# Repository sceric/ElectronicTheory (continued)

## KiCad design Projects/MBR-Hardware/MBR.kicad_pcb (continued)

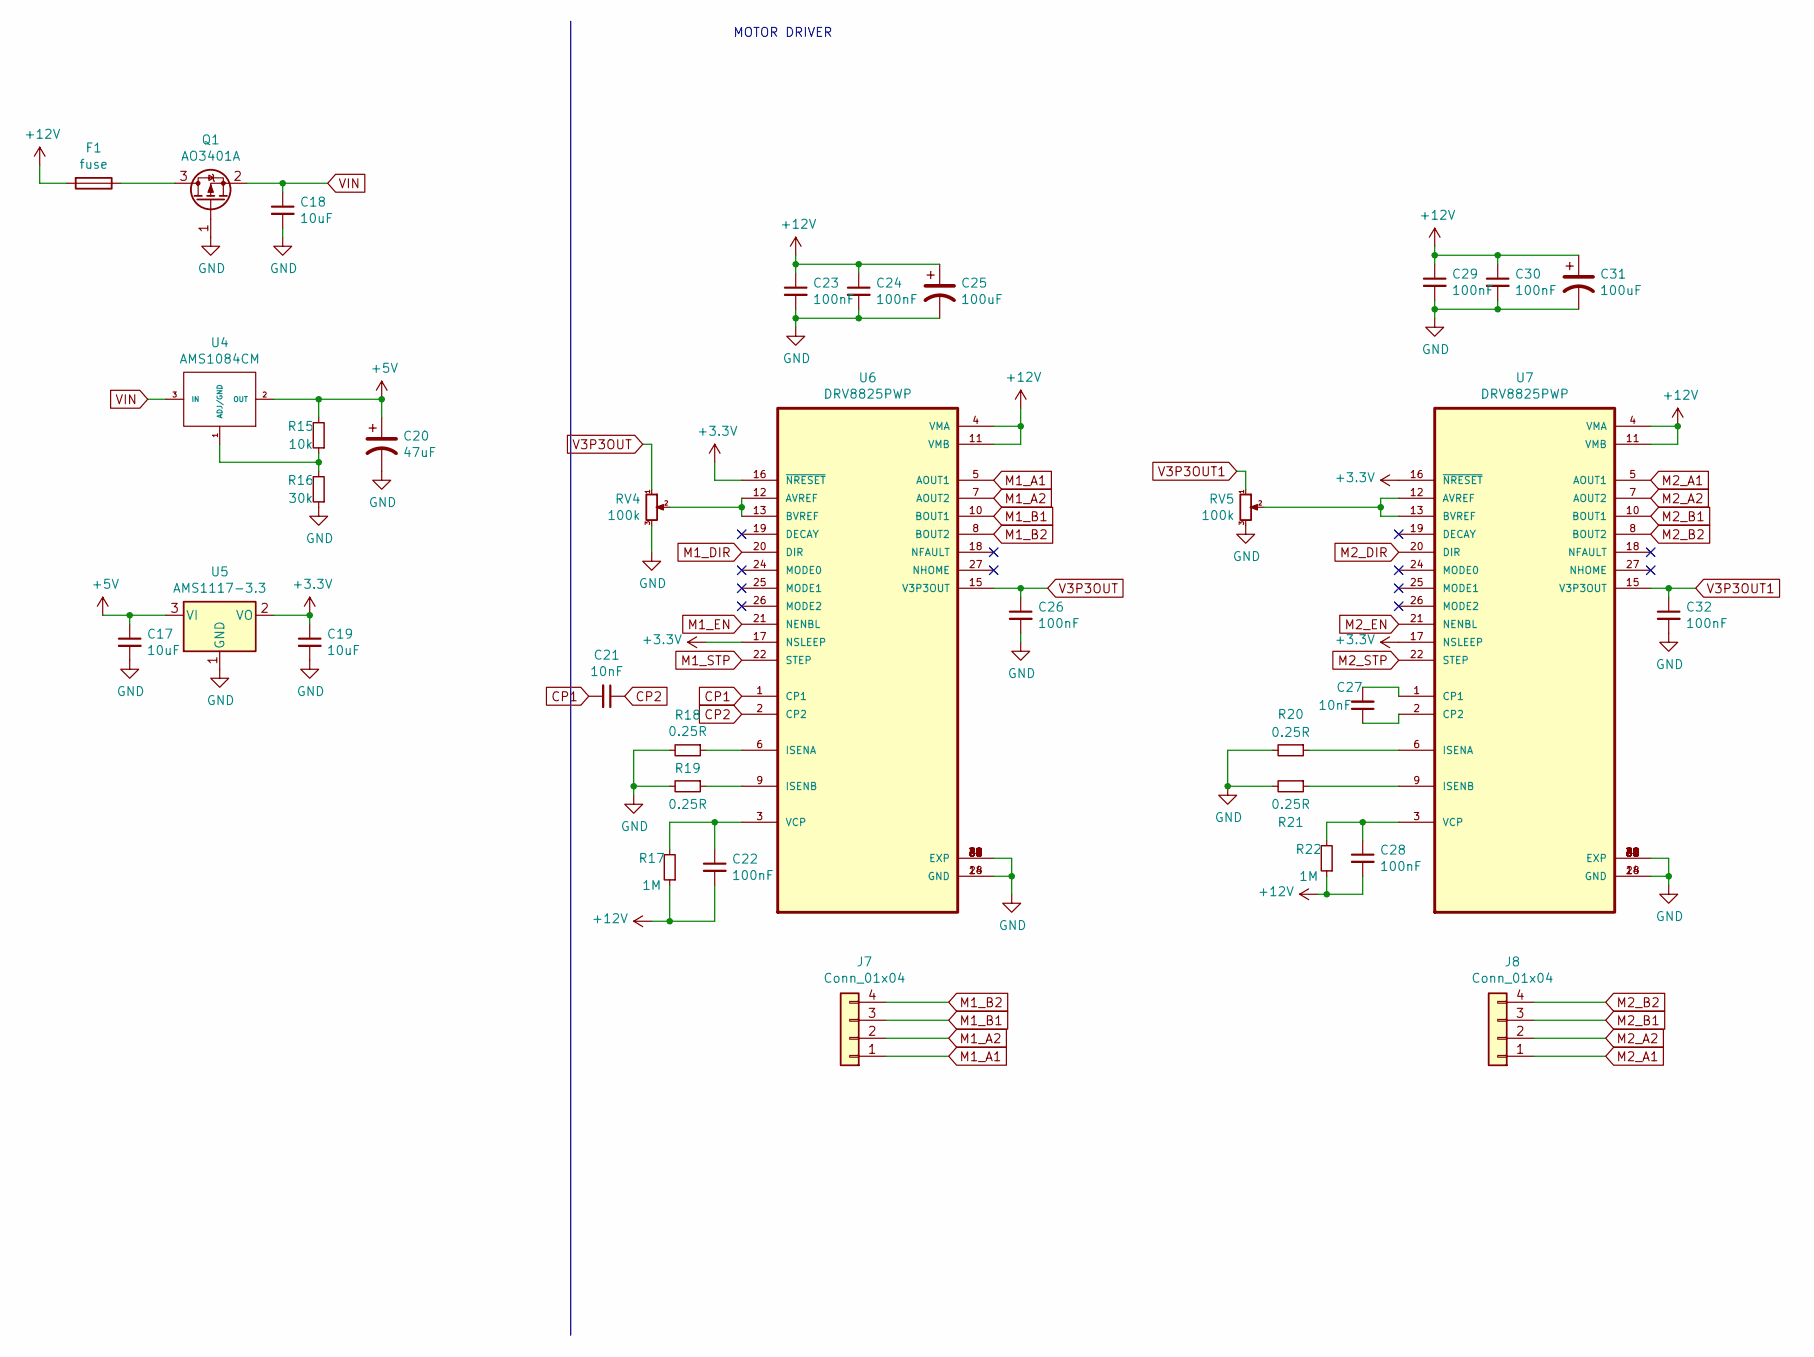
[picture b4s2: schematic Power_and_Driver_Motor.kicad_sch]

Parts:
C17, C18, C19: 10uF; C_0805_2012Metric
C20: 47uF; CP_Elec_6.3x5.4
C21, C27: 10nF; C_0603_1608Metric
C22, C23, C24, C26, C28, C29, C30, C32: 100nF; C_0603_1608Metric
C25, C31: 100uF; CP_Elec_8x10
F1: fuse; Fuse_1812_4532Metric
J7, J8: Conn_01x04; PinHeader_1x04_P2.54mm_Vertical
Q1: AO3401A; SOT-23
R15: 10k; R_0603_1608Metric
R16: 30k; R_0603_1608Metric
R17, R22: 1M; R_0603_1608Metric
R18, R19, R20, R21: 0.25R; R_0805_2012Metric
RV4, RV5: 100k; Potentiometer_Bourns_TC33X_Vertical
U4: AMS1084CM; TO-263-3_TabPin4
U5: AMS1117-3.3; SOT-223-3_TabPin2
U6, U7: DRV8825PWP; IC_TPS61196PWPRQ1

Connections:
+3V3: C19.1, U5.2 (VO), U6.16 (~NRESET), U6.17 (NSLEEP), U7.16 (~NRESET), U7.17 (NSLEEP); also elsewhere on the board
+5V: C17.1, C20.1, R15.2, U4.2 (OUT), U5.3 (VI); also elsewhere on the board
+12V: C22.2, C23.1, C24.1, C25.1, C28.2, C29.1, C30.1, C31.1, F1.2, R17.1, R22.1, U6.4 (VMA), U6.11 (VMB), U7.4 (VMA), U7.11 (VMB); also elsewhere on the board
CP1: C21.2, U6.1 (CP1)
CP2: C21.1, U6.2 (CP2)
GND: C17.2, C18.2, C19.2, C20.2, C23.2, C24.2, C25.2, C26.2, C29.2, C30.2, C31.2, C32.2, Q1.1 (G), R16.1, R18.2, R19.2, R20.2, R21.2, RV4.3, RV5.3, U5.1 (GND), U6.14 (GND), U6.28 (GND), U6.29 (EXP), U6.30 (EXP), U6.31 (EXP), U6.32 (EXP), U6.33 (EXP), U6.34 (EXP), U6.35 (EXP), U6.36 (EXP), U6.37 (EXP), U6.38 (EXP), U6.39 (EXP), U6.40 (EXP), U6.41 (EXP), U6.42 (EXP), U6.43 (EXP), U6.44 (EXP), U6.45 (EXP), U6.46 (EXP), U6.47 (EXP), U6.48 (EXP), U6.49 (EXP), U6.50 (EXP), U7.14 (GND), U7.28 (GND), U7.29 (EXP), U7.30 (EXP), U7.31 (EXP), U7.32 (EXP), U7.33 (EXP), U7.34 (EXP), U7.35 (EXP), U7.36 (EXP), U7.37 (EXP), U7.38 (EXP), U7.39 (EXP), U7.40 (EXP), U7.41 (EXP), U7.42 (EXP), U7.43 (EXP), U7.44 (EXP), U7.45 (EXP), U7.46 (EXP), U7.47 (EXP), U7.48 (EXP), U7.49 (EXP), U7.50 (EXP); also elsewhere on the board
M1_A1: J7.1, U6.5 (AOUT1)
M1_A2: J7.2, U6.7 (AOUT2)
M1_B1: J7.3, U6.10 (BOUT1)
M1_B2: J7.4, U6.8 (BOUT2)
M1_DIR: U6.20 (DIR); also elsewhere on the board
M1_EN: U6.21 (NENBL); also elsewhere on the board
M1_STP: U6.22 (STEP); also elsewhere on the board
M2_A1: J8.1, U7.5 (AOUT1)
M2_A2: J8.2, U7.7 (AOUT2)
M2_B1: J8.3, U7.10 (BOUT1)
M2_B2: J8.4, U7.8 (BOUT2)
M2_DIR: U7.20 (DIR); also elsewhere on the board
M2_EN: U7.21 (NENBL); also elsewhere on the board
M2_STP: U7.22 (STEP); also elsewhere on the board
unnamed: C22.1, R17.2, U6.3 (VCP)
unnamed: C27.1, U7.2 (CP2)
unnamed: C27.2, U7.1 (CP1)
unnamed: C28.1, R22.2, U7.3 (VCP)
unnamed: F1.1, Q1.3 (D)
unnamed: R15.1, R16.2, U4.1 (ADJ/GND)
unnamed: R18.1, U6.6 (ISENA)
unnamed: R19.1, U6.9 (ISENB)
unnamed: R20.1, U7.6 (ISENA)
unnamed: R21.1, U7.9 (ISENB)
unnamed: RV4.2, U6.12 (AVREF), U6.13 (BVREF)
unnamed: RV5.2, U7.12 (AVREF), U7.13 (BVREF)
V3P3OUT: C26.1, RV4.1, U6.15 (V3P3OUT)
V3P3OUT1: C32.1, RV5.1, U7.15 (V3P3OUT)
VIN: C18.1, Q1.2 (S), U4.3 (IN)

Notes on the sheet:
MOTOR DRIVER

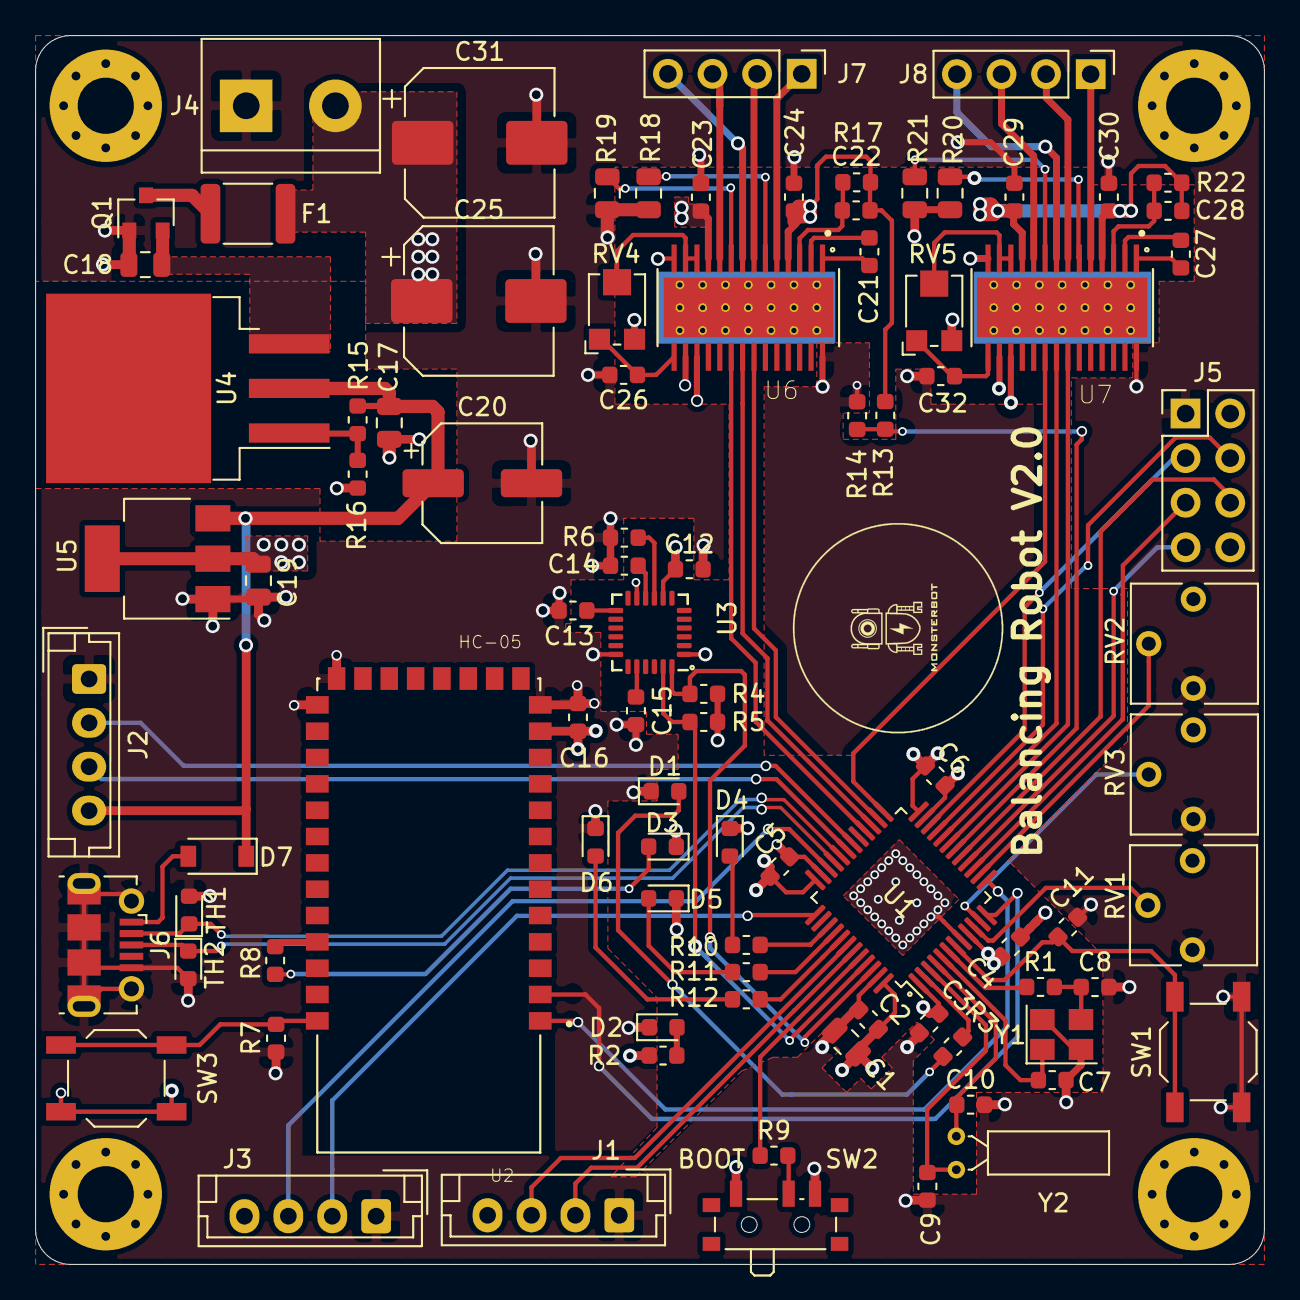
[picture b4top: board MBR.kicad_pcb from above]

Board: 4 copper layers, 70.0 x 70.0 mm, 94 parts (0 on the bottom side), 81 nets.

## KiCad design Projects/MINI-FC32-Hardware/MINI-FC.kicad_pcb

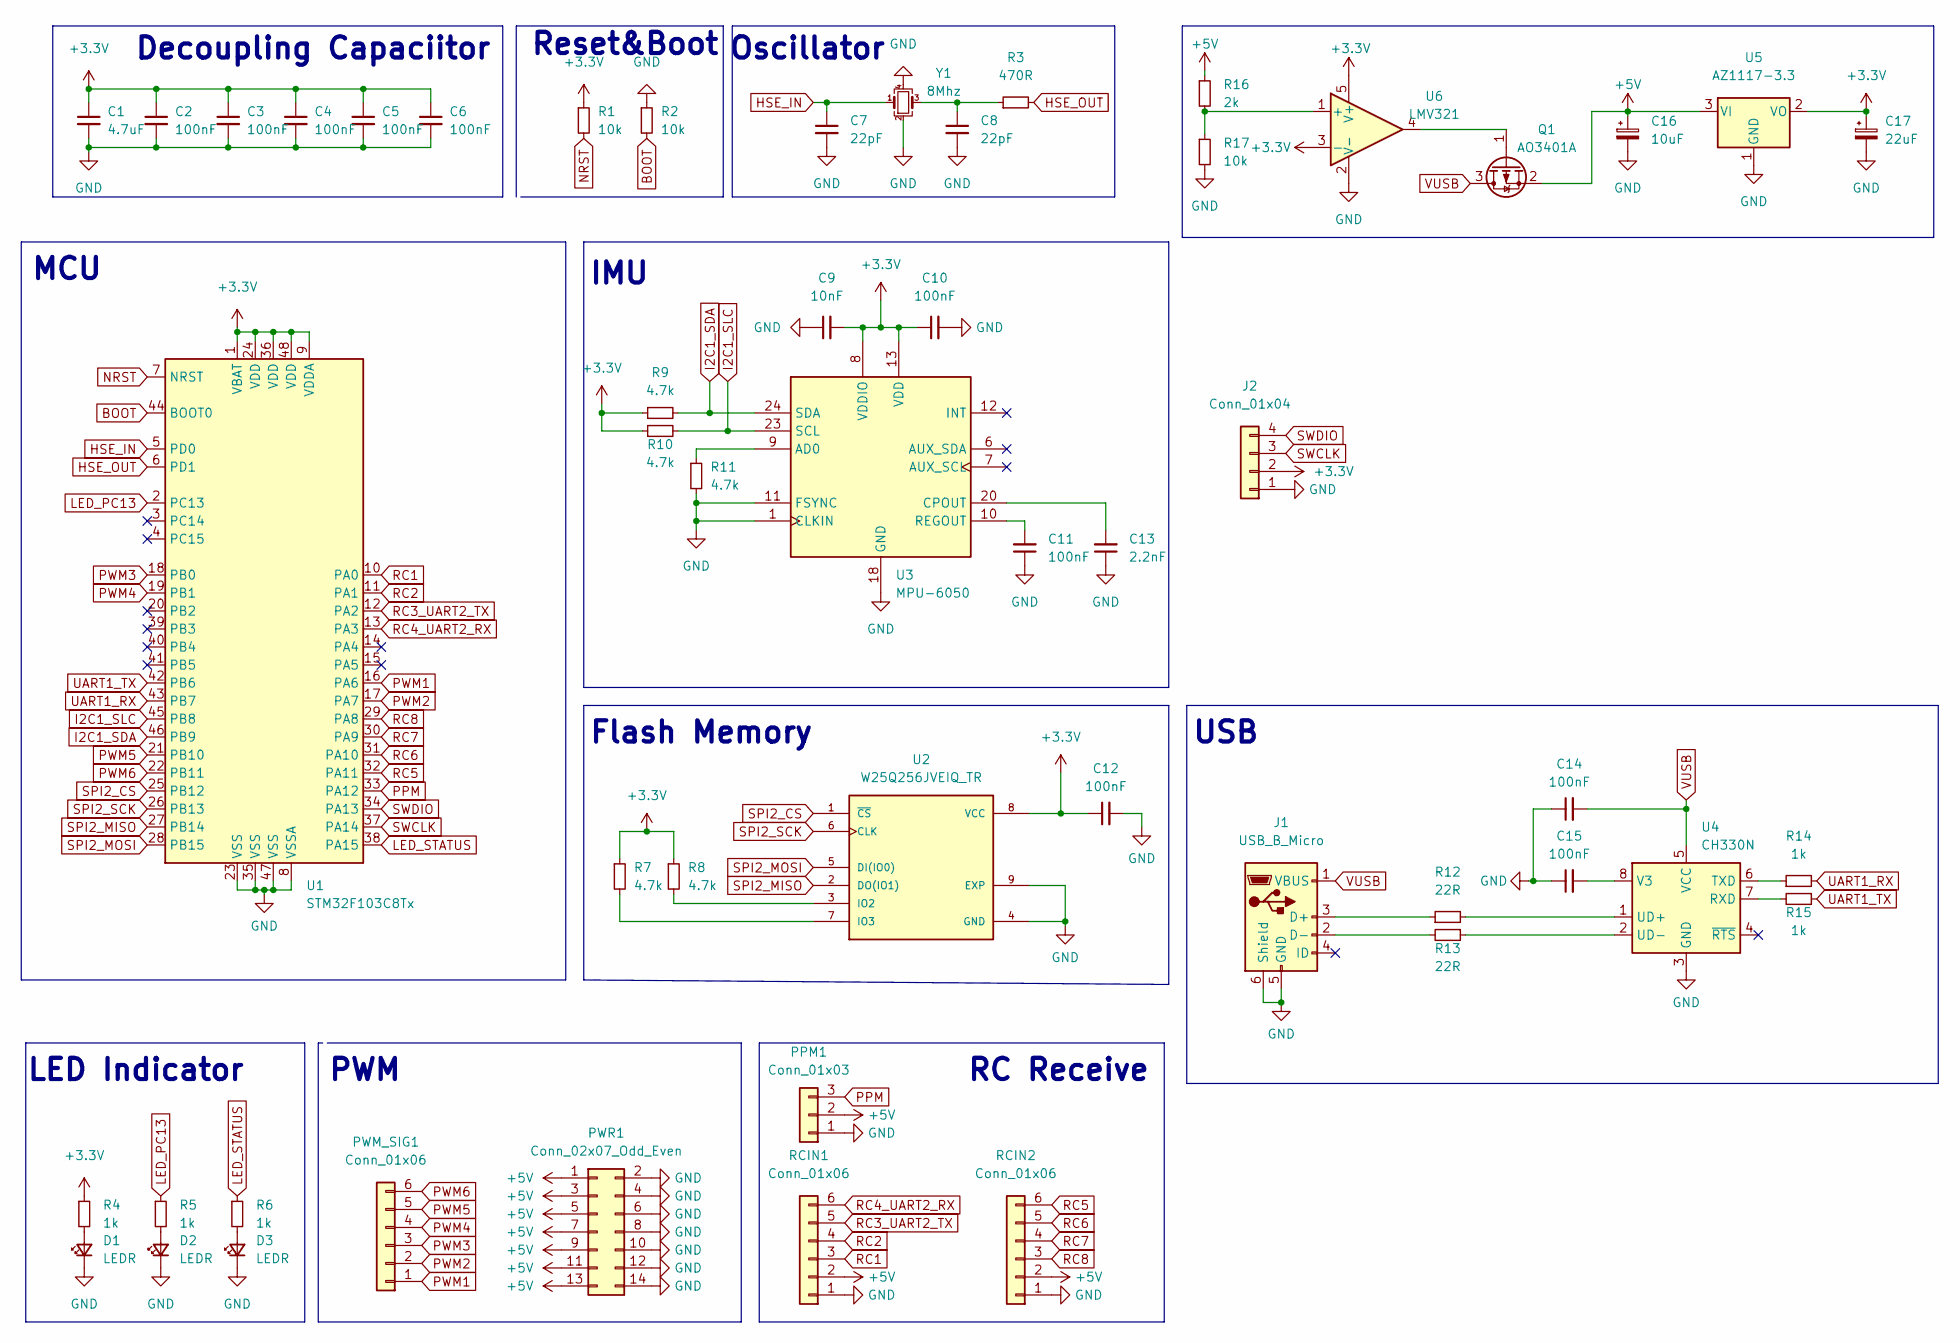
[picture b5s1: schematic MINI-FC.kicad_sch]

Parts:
C1: 4.7uF; C_0805_2012Metric
C2, C3, C4, C5, C6, C10, C11, C12, C14, C15: 100nF; C_0603_1608Metric
C7, C8: 22pF; C_0603_1608Metric
C9: 10nF; C_0603_1608Metric
C13: 2.2nF; C_0603_1608Metric
C16: 10uF; CP_EIA-3216-10_Kemet-I
C17: 22uF; CP_EIA-3216-10_Kemet-I
D1, D2, D3: LEDR; LED_0603_1608Metric
J1: USB_B_Micro; USB_Micro-B_Molex-105017-0001
J2: Conn_01x04; ConPadx04
PPM1: Conn_01x03; Molex_PicoBlade_53261-0371_1x03-1MP_P1.25mm_Horizontal
PWM_SIG1: Conn_01x06; PinHeader_1x06_P2.54mm_Vertical
PWR1: Conn_02x07_Odd_Even; PinHeader_2x07_P2.54mm_Vertical
Q1: AO3401A; SOT-23
R1, R2, R17: 10k; R_0603_1608Metric
R3: 470R; R_0603_1608Metric
R4, R5, R6, R14, R15: 1k; R_0603_1608Metric
R7, R8, R9, R10, R11: 4.7k; R_0603_1608Metric
R12, R13: 22R; R_0603_1608Metric
R16: 2k; R_0603_1608Metric
RCIN1, RCIN2: Conn_01x06; Molex_PicoBlade_53261-0671_1x06-1MP_P1.25mm_Horizontal
U1: STM32F103C8Tx; LQFP-48_7x7mm_P0.5mm
U2: W25Q256JVEIQ_TR; SON127P800X600X80-9N
U3: MPU-6050; InvenSense_QFN-24_4x4mm_P0.5mm
U4: CH330N; SOIC-8_3.9x4.9mm_P1.27mm
U5: AZ1117-3.3; SOT-89-3
U6: LMV321; SOT-23-5
Y1: 8Mhz; Crystal_SMD_3225-4Pin_3.2x2.5mm

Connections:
+3V3: C1.1, C2.1, C3.1, C4.1, C5.1, C6.1, C9.2, C10.1, C12.1, C17.1, J2.2, R1.1, R4.1, R7.1, R8.1, R9.1, R10.1, U1.1 (VBAT), U1.9 (VDDA), U1.24 (VDD), U1.36 (VDD), U1.48 (VDD), U2.8 (VCC), U3.8 (VDDIO), U3.13 (VDD), U5.2 (VO), U6.3 (-), U6.5 (V+)
+5V: C16.1, PPM1.2, PWR1.1, PWR1.3, PWR1.5, PWR1.7, PWR1.9, PWR1.11, PWR1.13, Q1.2 (S), R16.1, RCIN1.2, RCIN2.2, U5.3 (VI)
BOOT: R2.2, U1.44 (BOOT0)
GND: C1.2, C2.2, C3.2, C4.2, C5.2, C6.2, C7.2, C8.2, C9.1, C10.2, C11.1, C12.2, C13.1, C14.1, C15.1, C16.2, C17.2, D1.1 (K), D2.1 (K), D3.1 (K), J1.5 (GND), J1.6 (Shield), J2.1, PPM1.1, PWR1.2, PWR1.4, PWR1.6, PWR1.8, PWR1.10, PWR1.12, PWR1.14, R2.1, R11.2, R17.2, RCIN1.1, RCIN2.1, U1.8 (VSSA), U1.23 (VSS), U1.35 (VSS), U1.47 (VSS), U2.4 (GND), U2.9 (EXP), U3.1 (CLKIN), U3.11 (FSYNC), U3.18 (GND), U4.3 (GND), U5.1 (GND), U6.2 (V-), Y1.2, Y1.4
HSE_IN: C7.1, U1.5 (PD0), Y1.1
HSE_OUT: R3.2, U1.6 (PD1)
I2C1_SDA: R9.2, U1.46 (PB9), U3.24 (SDA)
I2C1_SLC: R10.2, U1.45 (PB8), U3.23 (SCL)
LED_PC13: R5.1, U1.2 (PC13)
LED_STATUS: R6.1, U1.38 (PA15)
NRST: R1.2, U1.7 (NRST)
unnamed: C8.1, R3.1, Y1.3
unnamed: C11.2, U3.10 (REGOUT)
unnamed: C13.2, U3.20 (CPOUT)
unnamed: C15.2, U4.8 (V3)
unnamed: D1.2 (A), R4.2
unnamed: D2.2 (A), R5.2
unnamed: D3.2 (A), R6.2
unnamed: J1.2 (D-), R13.2
unnamed: J1.3 (D+), R12.1
unnamed: Q1.1 (G), U6.4
unnamed: R7.2, U2.7 (IO3)
unnamed: R8.2, U2.3 (IO2)
unnamed: R11.1, U3.9 (AD0)
unnamed: R12.2, U4.1 (UD+)
unnamed: R13.1, U4.2 (UD-)
unnamed: R14.1, U4.6 (TXD)
unnamed: R15.2, U4.7 (RXD)
unnamed: R16.2, R17.1, U6.1 (+)
PPM: PPM1.3, U1.33 (PA12)
PWM1: PWM_SIG1.1, U1.16 (PA6)
PWM2: PWM_SIG1.2, U1.17 (PA7)
PWM3: PWM_SIG1.3, U1.18 (PB0)
PWM4: PWM_SIG1.4, U1.19 (PB1)
PWM5: PWM_SIG1.5, U1.21 (PB10)
PWM6: PWM_SIG1.6, U1.22 (PB11)
RC1: RCIN1.3, U1.10 (PA0)
RC2: RCIN1.4, U1.11 (PA1)
RC3_UART2_TX: RCIN1.5, U1.12 (PA2)
RC4_UART2_RX: RCIN1.6, U1.13 (PA3)
RC5: RCIN2.6, U1.32 (PA11)
RC6: RCIN2.5, U1.31 (PA10)
RC7: RCIN2.4, U1.30 (PA9)
RC8: RCIN2.3, U1.29 (PA8)
SPI2_CS: U1.25 (PB12), U2.1 (~CS)
SPI2_MISO: U1.27 (PB14), U2.2 (DO(IO1))
SPI2_MOSI: U1.28 (PB15), U2.5 (DI(IO0))
SPI2_SCK: U1.26 (PB13), U2.6 (CLK)
SWCLK: J2.3, U1.37 (PA14)
SWDIO: J2.4, U1.34 (PA13)
UART1_RX: R14.2, U1.43 (PB7)
UART1_TX: R15.1, U1.42 (PB6)
VUSB: C14.2, J1.1 (VBUS), Q1.3 (D), U4.5 (VCC)

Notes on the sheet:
Decoupling Capaciitor
MCU
LED Indicator
USB
Reset&Boot
RC Receive
PWM
IMU
Flash Memory
Oscillator

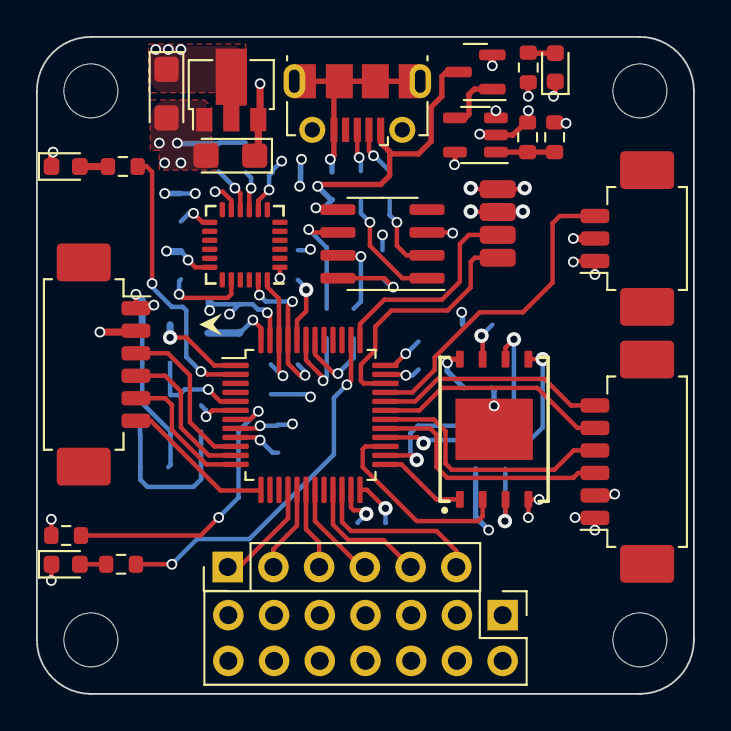
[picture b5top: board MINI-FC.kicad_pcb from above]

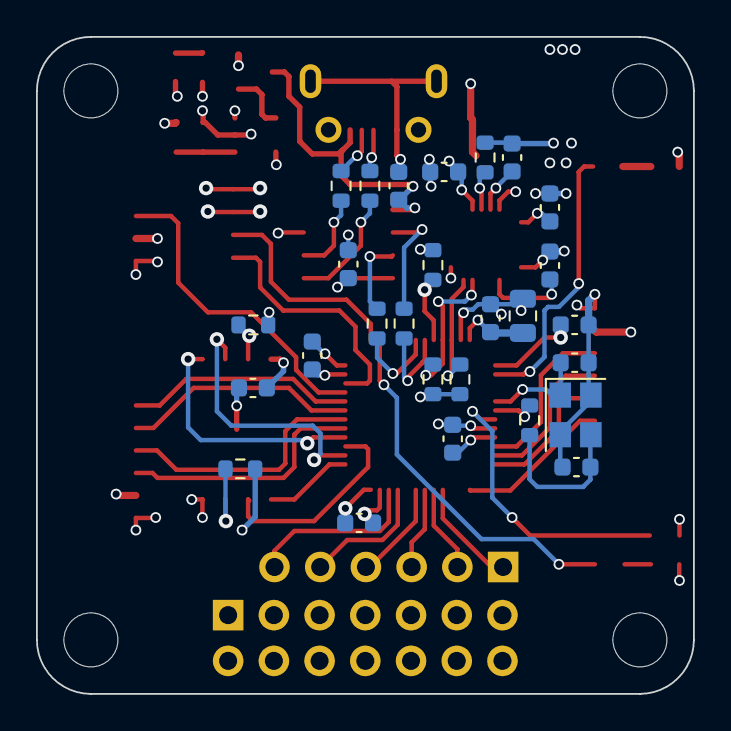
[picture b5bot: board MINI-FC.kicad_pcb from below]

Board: 4 copper layers, 36.5 x 36.5 mm, 52 parts (27 on the bottom side), 53 nets.

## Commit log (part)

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2022-02-12 Update with new files
2022-09-07 Updated 220907
2022-09-27 Updated 220927
2022-10-05 Update 221005
2022-10-09 Update 221009
2022-10-23 Update 221023
2022-11-01 Update 221101
2022-11-20 Update 221120
2023-02-25 Updated 230225
2023-05-23 Updated 230523
2024-01-11 Added map Books I
2025-03-16 Add new documets
2025-04-22 Added new books
2025-05-13 Added new files
2025-06-28 Added files
2025-09-19 Added new and updated files
